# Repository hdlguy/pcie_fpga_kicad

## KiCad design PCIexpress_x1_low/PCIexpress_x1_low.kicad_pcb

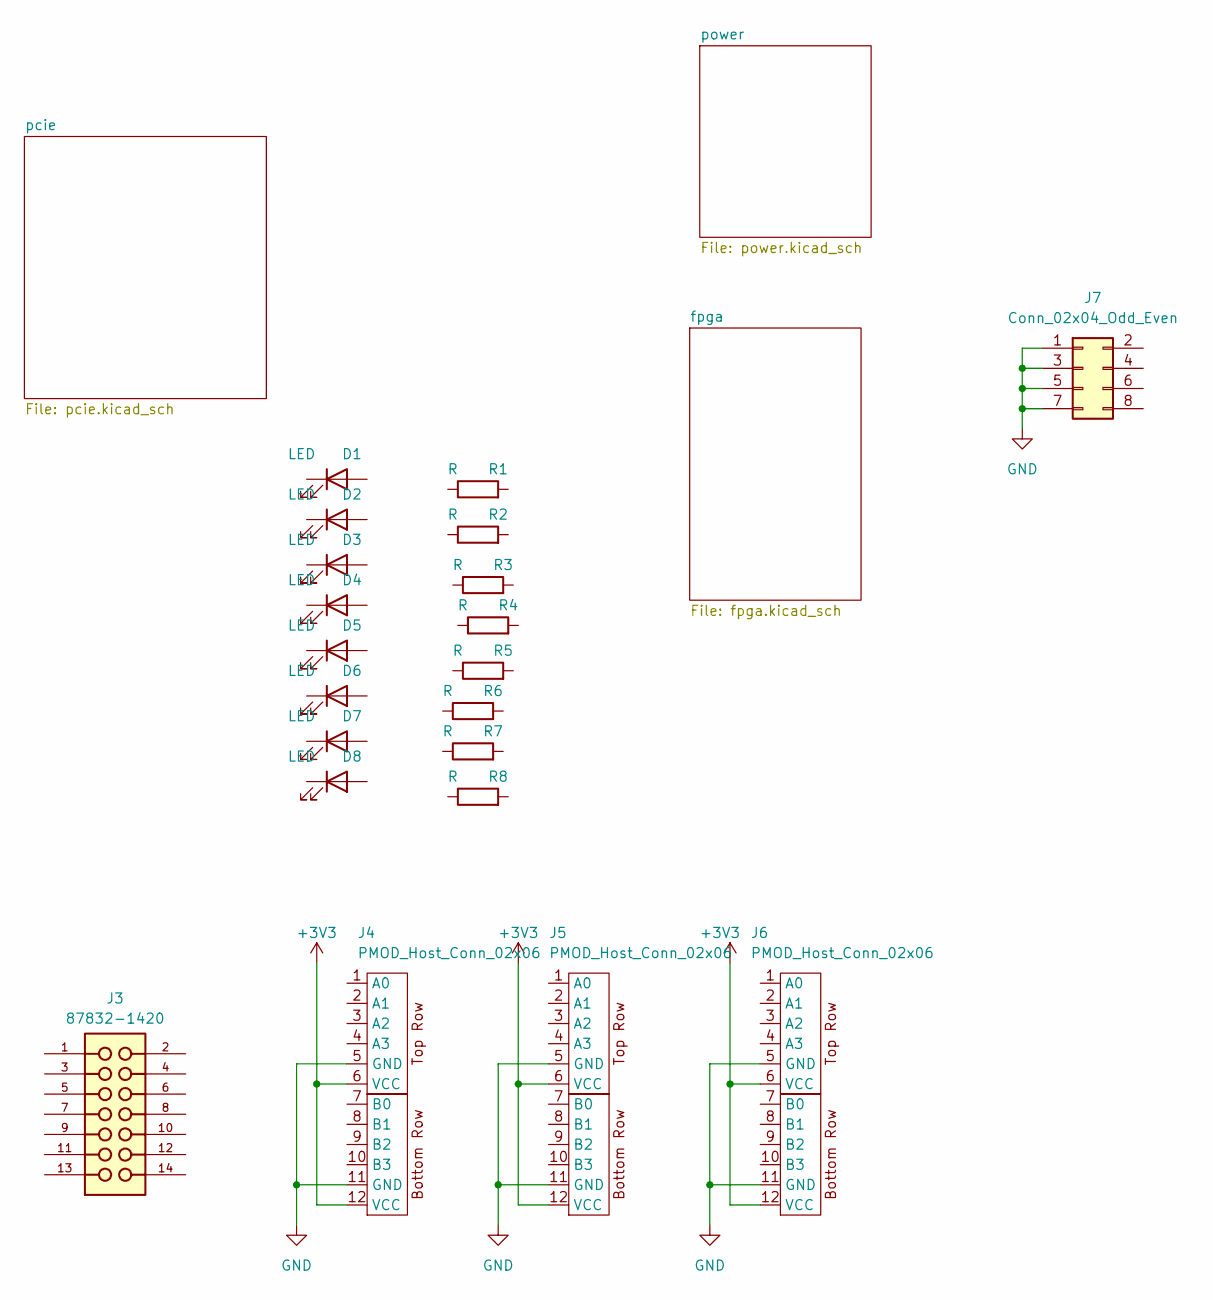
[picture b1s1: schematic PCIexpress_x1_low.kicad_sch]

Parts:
D1, D2, D3, D4, D5, D6, D7, D8: LED; LED_0603_1608Metric
J3: 87832-1420; MOLEX_87832-1420
J4, J5, J6: PMOD_Host_Conn_02x06; PMOD_PinSocket_2x06_P2.54mm_Horizontal
J7: Conn_02x04_Odd_Even; PinHeader_2x04_P2.54mm_Vertical
R1, R2, R3, R4, R5, R6, R7, R8: R; R_0603_1608Metric

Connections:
+3V3: J4.6 (VCC), J4.12 (VCC), J5.6 (VCC), J5.12 (VCC), J6.6 (VCC), J6.12 (VCC)
GND: J4.5 (GND), J4.11 (GND), J5.5 (GND), J5.11 (GND), J6.5 (GND), J6.11 (GND), J7.1, J7.3, J7.5, J7.7; also elsewhere on the board

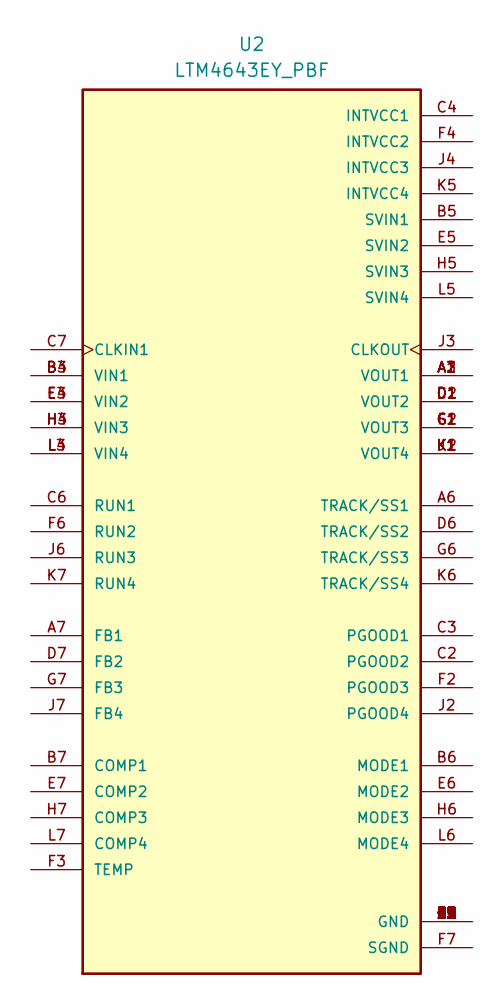
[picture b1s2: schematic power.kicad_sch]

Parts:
U2: LTM4643EY_PBF; BGA77C127P7X11_1500X900X262; PART_REV B

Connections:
unnamed: U2.A4 (GND), U2.A5 (GND), U2.B1 (GND), U2.B2 (GND), U2.C5 (GND), U2.D3 (GND), U2.D4 (GND), U2.D5 (GND), U2.E1 (GND), U2.E2 (GND), U2.F5 (GND), U2.G3 (GND), U2.G4 (GND), U2.G5 (GND), U2.H1 (GND), U2.H2 (GND), U2.J5 (GND), U2.K3 (GND), U2.K4 (GND), U2.L1 (GND), U2.L2 (GND)
unnamed: U2.B3 (VIN1), U2.B4 (VIN1)
unnamed: U2.E3 (VIN2), U2.E4 (VIN2)
unnamed: U2.H3 (VIN3), U2.H4 (VIN3)
unnamed: U2.L3 (VIN4), U2.L4 (VIN4)
unnamed: U2.A1 (VOUT1), U2.A2 (VOUT1), U2.A3 (VOUT1)
unnamed: U2.C1 (VOUT2), U2.D1 (VOUT2), U2.D2 (VOUT2)
unnamed: U2.F1 (VOUT3), U2.G1 (VOUT3), U2.G2 (VOUT3)
unnamed: U2.J1 (VOUT4), U2.K1 (VOUT4), U2.K2 (VOUT4)

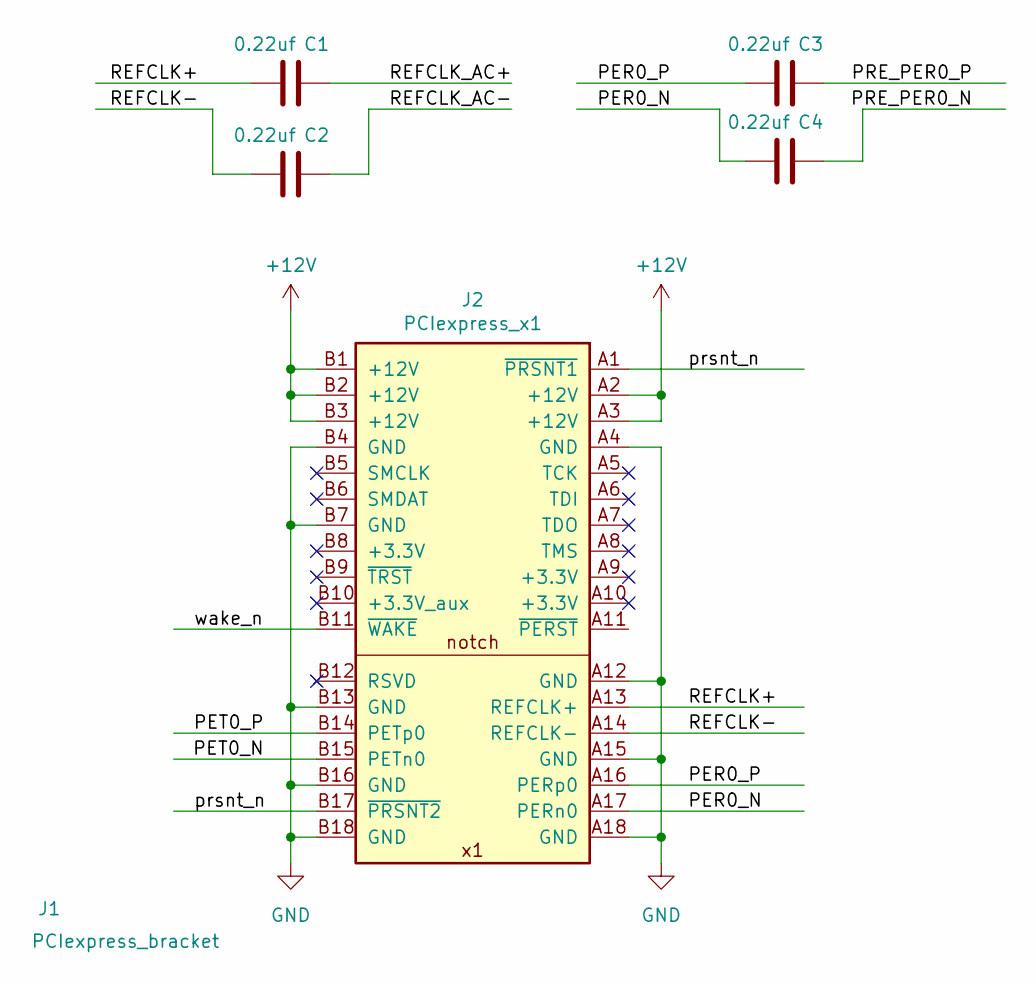
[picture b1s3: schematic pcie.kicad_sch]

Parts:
C1, C2, C3, C4: 0.22uf; C_0402_1005Metric
J1: PCIexpress_bracket; PCIexpress_bracket_low
J2: PCIexpress_x1

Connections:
+12V: J2.A2 (+12V), J2.A3 (+12V), J2.B1 (+12V), J2.B2 (+12V), J2.B3 (+12V)
/pcie/PER0_N: C4.1, J2.A17 (PERn0)
/pcie/PER0_P: C3.1, J2.A16 (PERp0)
/pcie/PET0_N: J2.B15 (PETn0)
/pcie/PET0_P: J2.B14 (PETp0)
/pcie/PRE_PER0_N: C4.2
/pcie/PRE_PER0_P: C3.2
/pcie/REFCLK+: C1.1, J2.A13 (REFCLK+)
/pcie/REFCLK-: C2.1, J2.A14 (REFCLK-)
/pcie/REFCLK_AC+: C1.2
/pcie/REFCLK_AC-: C2.2
/pcie/prsnt_n: J2.A1 (~PRSNT1), J2.B17 (~PRSNT2)
/pcie/wake_n: J2.B11 (~WAKE)
GND: J2.A4 (GND), J2.A12 (GND), J2.A15 (GND), J2.A18 (GND), J2.B4 (GND), J2.B7 (GND), J2.B13 (GND), J2.B16 (GND), J2.B18 (GND); also elsewhere on the board

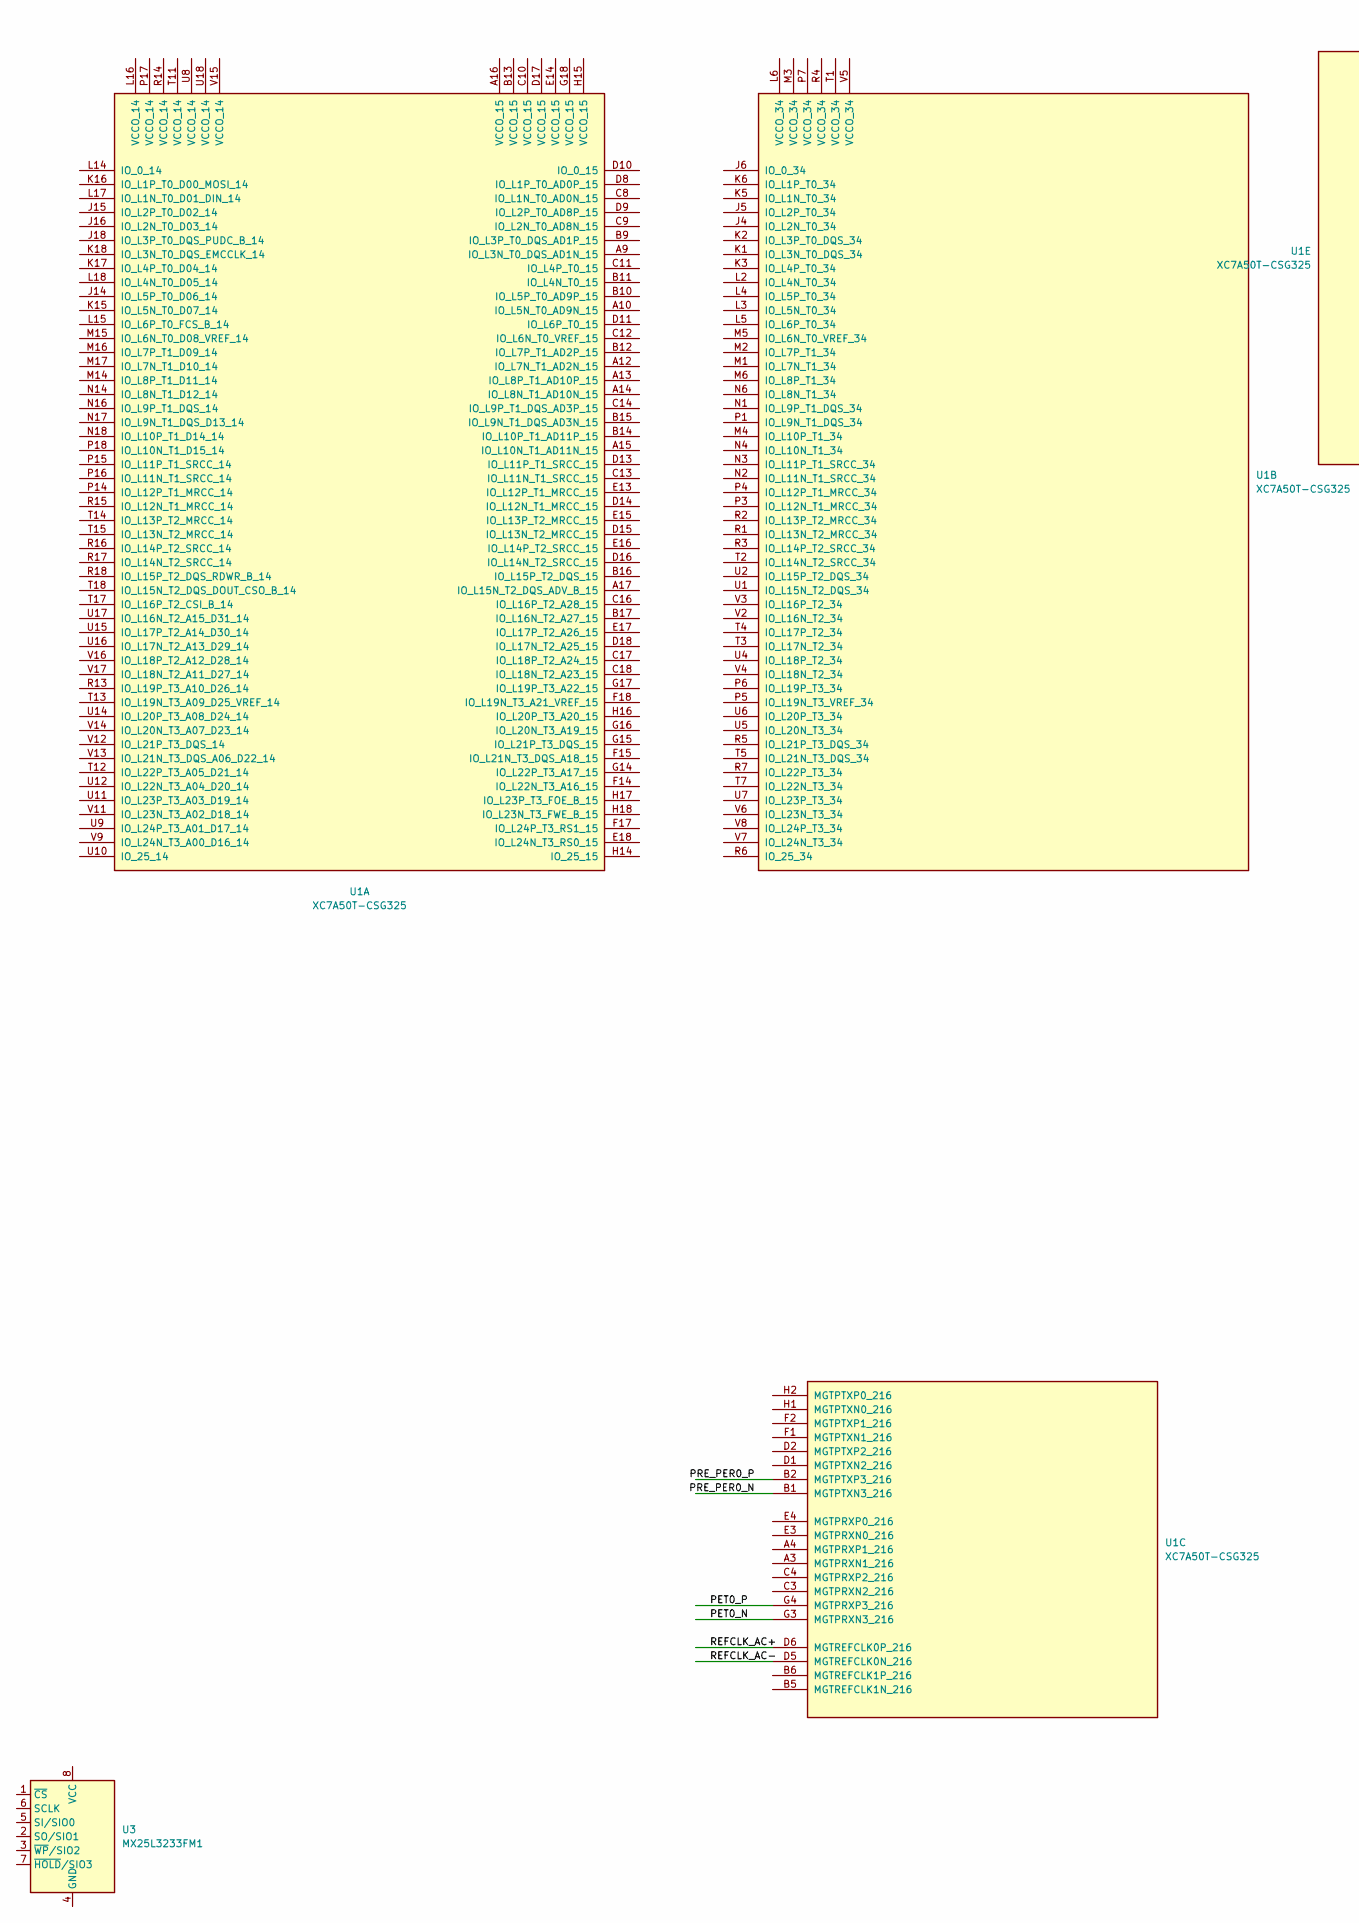
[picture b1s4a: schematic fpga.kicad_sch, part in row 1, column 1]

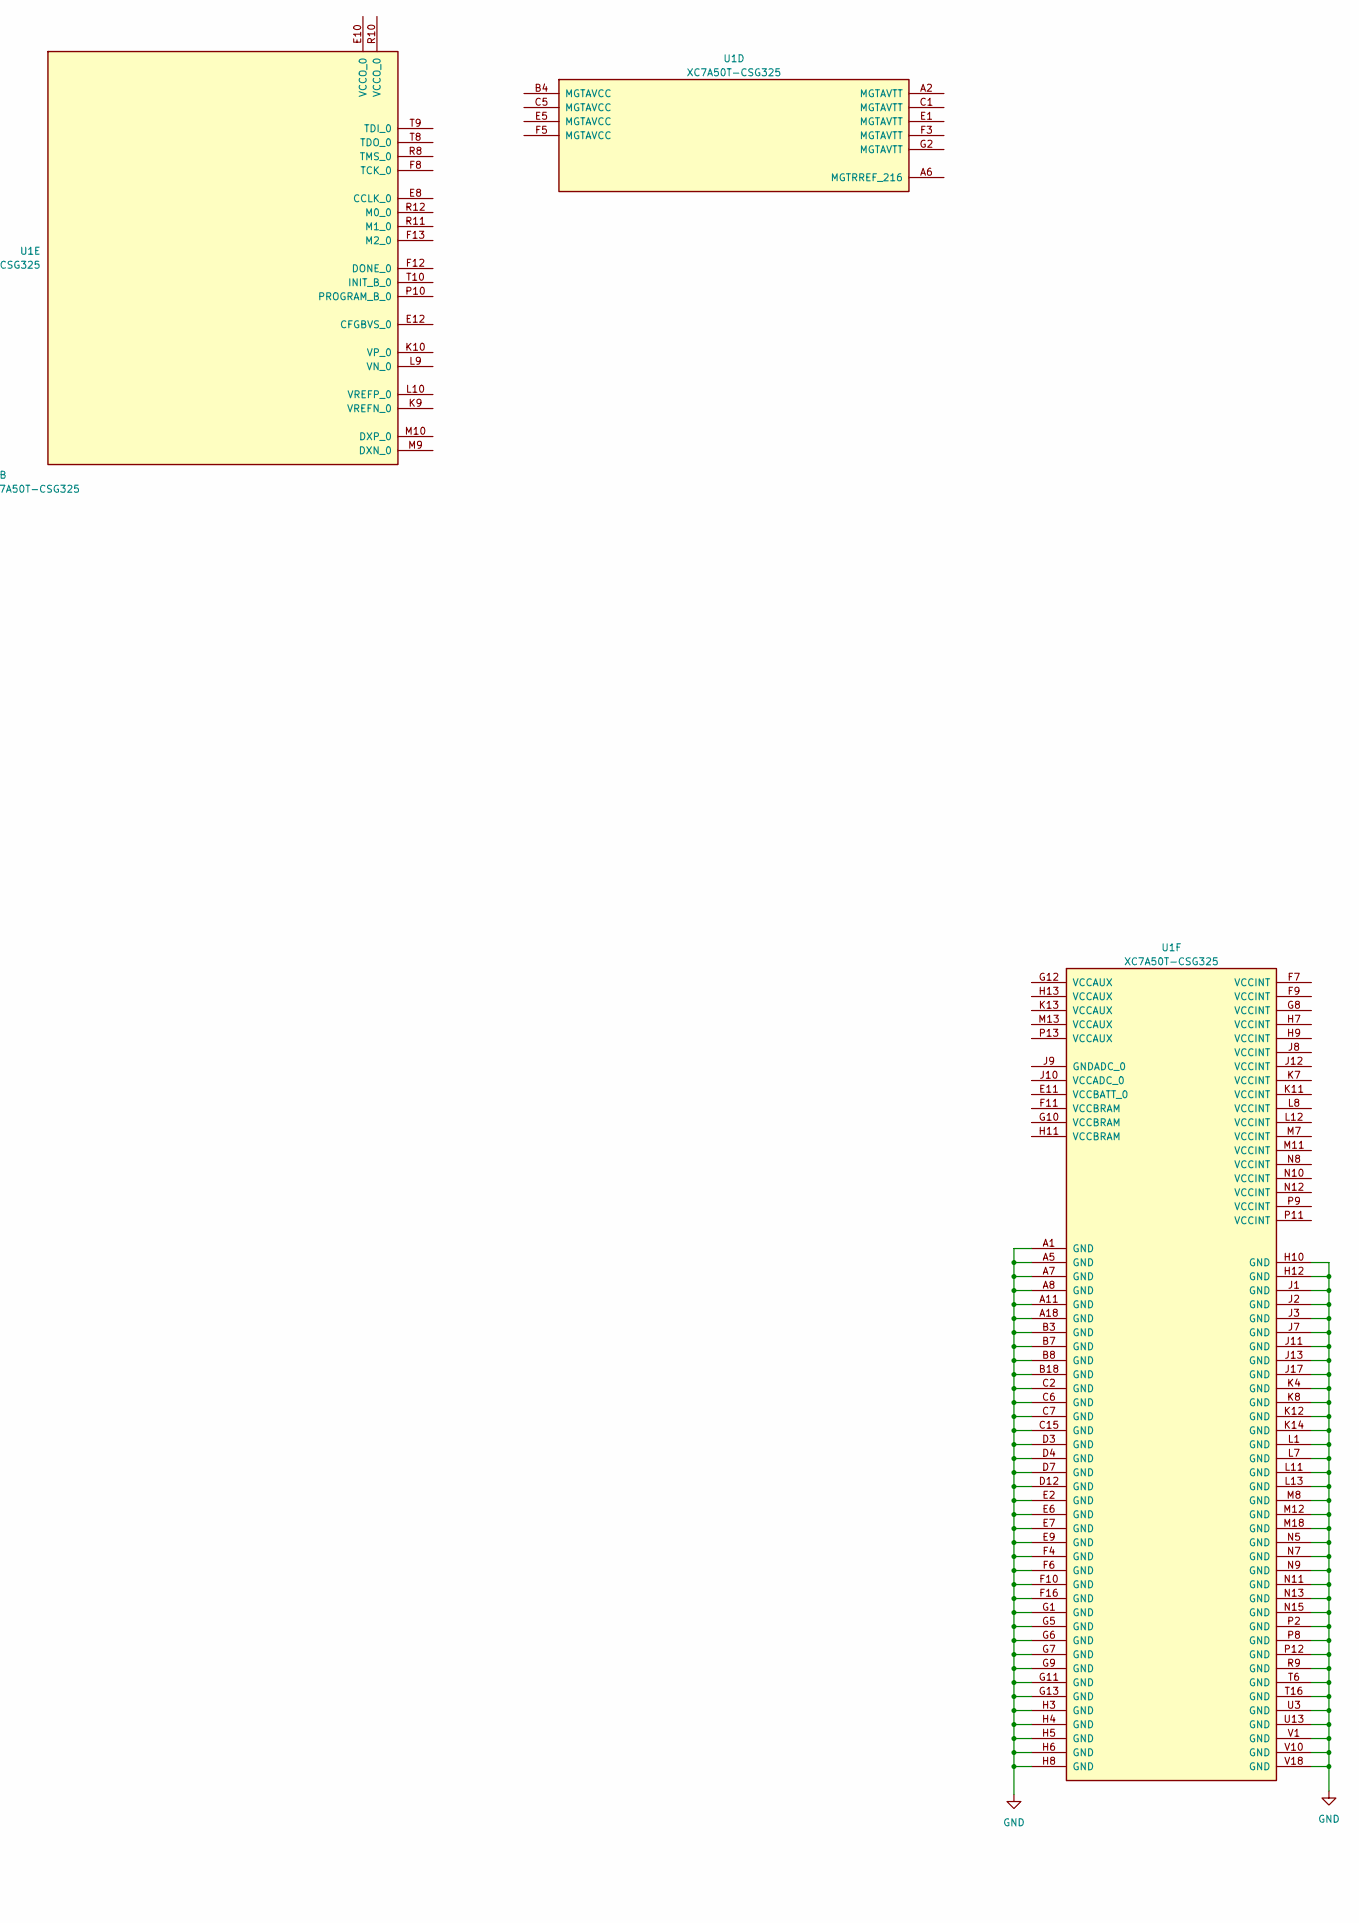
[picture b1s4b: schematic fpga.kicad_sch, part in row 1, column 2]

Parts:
U1: XC7A50T-CSG325; Xilinx_CSG325
U3: MX25L3233FM1; SOP-8_3.9x4.9mm_P1.27mm

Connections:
/fpga/PET0_N: U1.G3 (MGTPRXN3_216)
/fpga/PET0_P: U1.G4 (MGTPRXP3_216)
/fpga/PRE_PER0_N: U1.B1 (MGTPTXN3_216)
/fpga/PRE_PER0_P: U1.B2 (MGTPTXP3_216)
/fpga/REFCLK_AC+: U1.D6 (MGTREFCLK0P_216)
/fpga/REFCLK_AC-: U1.D5 (MGTREFCLK0N_216)
GND: U1.A1 (GND), U1.A5 (GND), U1.A7 (GND), U1.A8 (GND), U1.A11 (GND), U1.A18 (GND), U1.B3 (GND), U1.B7 (GND), U1.B8 (GND), U1.B18 (GND), U1.C2 (GND), U1.C6 (GND), U1.C7 (GND), U1.C15 (GND), U1.D3 (GND), U1.D4 (GND), U1.D7 (GND), U1.D12 (GND), U1.E2 (GND), U1.E6 (GND), U1.E7 (GND), U1.E9 (GND), U1.F4 (GND), U1.F6 (GND), U1.F10 (GND), U1.F16 (GND), U1.G1 (GND), U1.G5 (GND), U1.G6 (GND), U1.G7 (GND), U1.G9 (GND), U1.G11 (GND), U1.G13 (GND), U1.H3 (GND), U1.H4 (GND), U1.H5 (GND), U1.H6 (GND), U1.H8 (GND), U1.H10 (GND), U1.H12 (GND), U1.J1 (GND), U1.J2 (GND), U1.J3 (GND), U1.J7 (GND), U1.J11 (GND), U1.J13 (GND), U1.J17 (GND), U1.K4 (GND), U1.K8 (GND), U1.K12 (GND), U1.K14 (GND), U1.L1 (GND), U1.L7 (GND), U1.L11 (GND), U1.L13 (GND), U1.M8 (GND), U1.M12 (GND), U1.M18 (GND), U1.N5 (GND), U1.N7 (GND), U1.N9 (GND), U1.N11 (GND), U1.N13 (GND), U1.N15 (GND), U1.P2 (GND), U1.P8 (GND), U1.P12 (GND), U1.R9 (GND), U1.T6 (GND), U1.T16 (GND), U1.U3 (GND), U1.U13 (GND), U1.V1 (GND), U1.V10 (GND), U1.V18 (GND); also elsewhere on the board

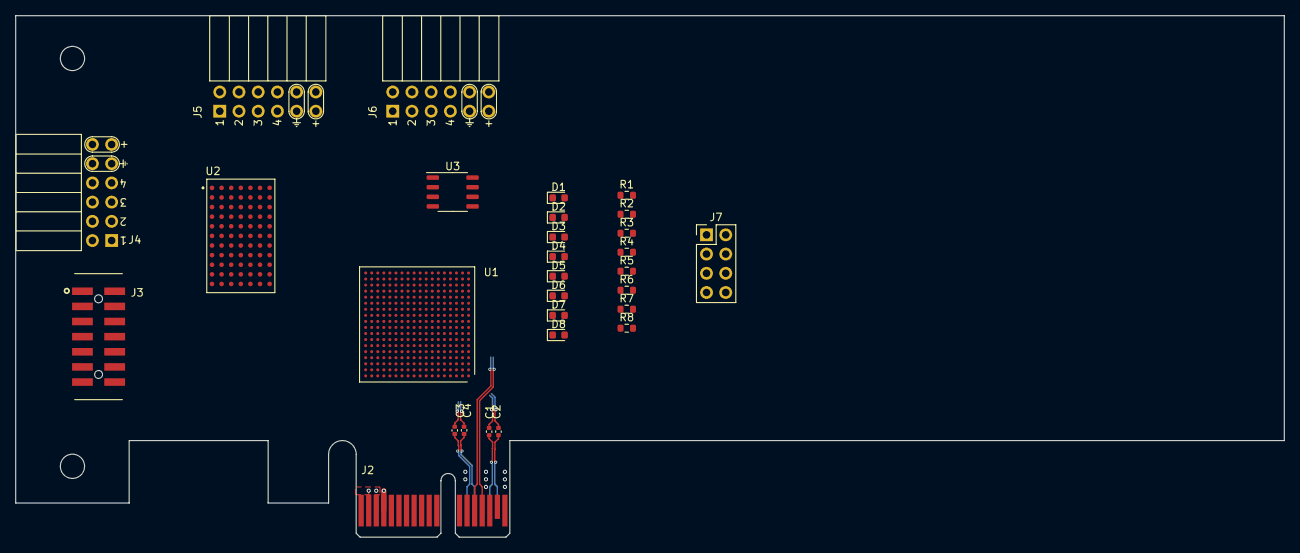
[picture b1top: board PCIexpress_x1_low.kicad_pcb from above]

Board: 6 copper layers, 167.7 x 68.9 mm, 30 parts (0 on the bottom side), 17 nets.

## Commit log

2024-01-19 saved as KiCad 7 project
2024-01-19 working to route 0.8mm pitch bga, probably not practical
2024-01-21 looks liket the xilinx csg325 package can route in Oshpark 6 layer stackup
2024-01-22 added pmic and config flash
2024-01-22 threw down some LEDs
2024-01-23 adding AC coupling caps
2024-01-24 using hierarchal sheets
2026-02-08 Add MIT License to the project
